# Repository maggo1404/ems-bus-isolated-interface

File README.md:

# Optocoupler Isolated EMS Bus Interface for ESP32 / Raspberry Pi

An open-source hardware interface designed to safely connect microcontrollers (like ESP32 or Raspberry Pi) to the **EMS (Energy Management System)** bus used by Bosch, Buderus, Junkers, IVT and Nefit heating systems.

## Key Features

* **Galvanic Isolation:** Full optical/digital isolation protecting your microcontroller and smart home infrastructure from high-voltage spikes or ground loops on the boiler side.
* **4-Pin Output Interface:** Simple connection via `GND`, `Rx`, `Tx`, and `3.3V`.
* **High Compatibility:** Designed to be fully compatible with popular open-source firmware [EMS-ESP32](https://github.com/emsesp/EMS-ESP32).
* **Compact DIY Design:** Two-layer PCB created in Autodesk Eagle, optimized for easy manual soldering or cheap fabrication (JLCPCB, PCBWay).

---

## Technical Specifications

* **Input:** 2-wire EMS Bus (Non-polarized)
* **Output:** 3.3V Logic Levels (`Rx` from EMS to MCU, `Tx` from MCU to EMS)
* **Power Supply:** 
  * EMS Side: Powered directly from the EMS bus line.
  * MCU Side: Powered from the connected microcontroller via the `3.3V` pin (requires approx. 10 mA).
* **Isolation Voltage:** Min 3 kV (achieved via optocouplers 6N137 and 6N136).

---

## Repository Structure

* `/hardware` - Original Autodesk Eagle design files (`.sch`, `.brd` and `.lbr`).
* `/gerber` - Production-ready Gerber and Drill files (Excellon) for easy PCB manufacturing.
* `/bom` - Bill of Materials with component specifications.
* `/assets` - Images and pdf files.

---

## Schematic & PCB Preview
You can notice the strict galvanic isolation of both parts. They are bridged only by optocouplers.

---

## How to Order and Build

1. **Manufacture the PCB:** Download the ZIP file from the `/gerber` folder and upload it to any PCB manufacturer (e.g., JLCPCB, PCBWay, OSH Park). Choose a standard 1.6mm thickness, 2-layer option.
2. **Buy Components:** Refer to the [BOM.csv](./bom/BOM.csv) or [BOM.pdf](./bom/BOM.pdf) file for the exact part list. 
3. **Assembly:** Solder the components starting from the lowest profile parts (resistors, diodes) to the highest (connectors, optocouplers).

---

## Connection Diagram

### EMS Bus Side
Connect the 2-wire terminal to your boiler's EMS service jack or thermostat line.

### Microcontroller Side (e.g., ESP32 running EMS-ESP)

| Interface Pin | ESP32 Pin | Description |
| --- | --- | --- |
| **GND** | GND | Ground reference (isolated side) |
| **Rx** | GPIO 5 (Rx) | Connect to ESP32 Rx pin |
| **Tx** | GPIO 17 (Tx) | Connect to ESP32 Tx pin |
| **3.3V** | 3.3V | Power input for the isolated side |

---

## Software Integration

This hardware is verified to work with:
* **EMS-ESP32 Firmware:** Set the board profile to *Custom* and configure your chosen Rx/Tx pins in the web interface.

---

## Notes on some components

**C12 - 2200µF/25V**  
Originally I wanted to use a capacitor with a capacity of 1000µF. During testing, everything seemed to be fine. However, for dimensional reasons, I also tried a capacitor with a capacity of 470µF, because it fit into the intended box even in the normal position ("vertical"). However, in practice it turned out that with this capacitor the communication error rate increased sharply. Of course, this was not desirable, so I used a larger capacitor (with sufficient margin).

**OC1 and OC2 - 6N137 and 6N136**  
For the Rx direction (EMS -> ESP32), I chose an optocoupler of the 6N137SM-ISO type. It is fast enough and guarantees problem-free communication. In the opposite direction, the cheaper 6N136S-TA1-L is more than enough. Both optocouplers are in an SMD8 package with gull-wing pins.

**R2, R3 and R4 - 68Ω**  
The resistors are in a R2010 type case, so they should last with a large margin. Regular resistors in a R0805 case would be overloaded if used in this way and the connection would not be reliable in the long term.

**U1 - LM393**  
I used the LMV393IDR type.
It is fast enough, suitable for 5V power supply, has low consumption and has open collector outputs.

**U2 - JW5017S**  
You can also use the (perhaps more affordable) RY8310.

---

## Assembled board
Finally, you can see some photos of the fully assembled PCB including the installation in the box and the connection to the ESP32-S3 development kit. I have also added one screenshot showing the statistics of Data Traffic after about 90 hours of operation.

---

## License & Disclaimer

This project is licensed under the Creative Commons Attribution-NonCommercial-ShareAlike 4.0 International License (CC BY-NC-SA 4.0). 

* **Non-Commercial:** The hardware design files were created using the free/personal-use tier of Autodesk Eagle and are strictly intended for non-commercial, educational, and DIY purposes.
* **ShareAlike:** If you remix, transform, or build upon the material, you must distribute your contributions under the same license.

**Disclaimer:** Working with heating appliances carries inherent risks. Improper connection can damage your boiler's mainboard. Use this hardware at your own risk. The author is not responsible for any damage caused by using this design.

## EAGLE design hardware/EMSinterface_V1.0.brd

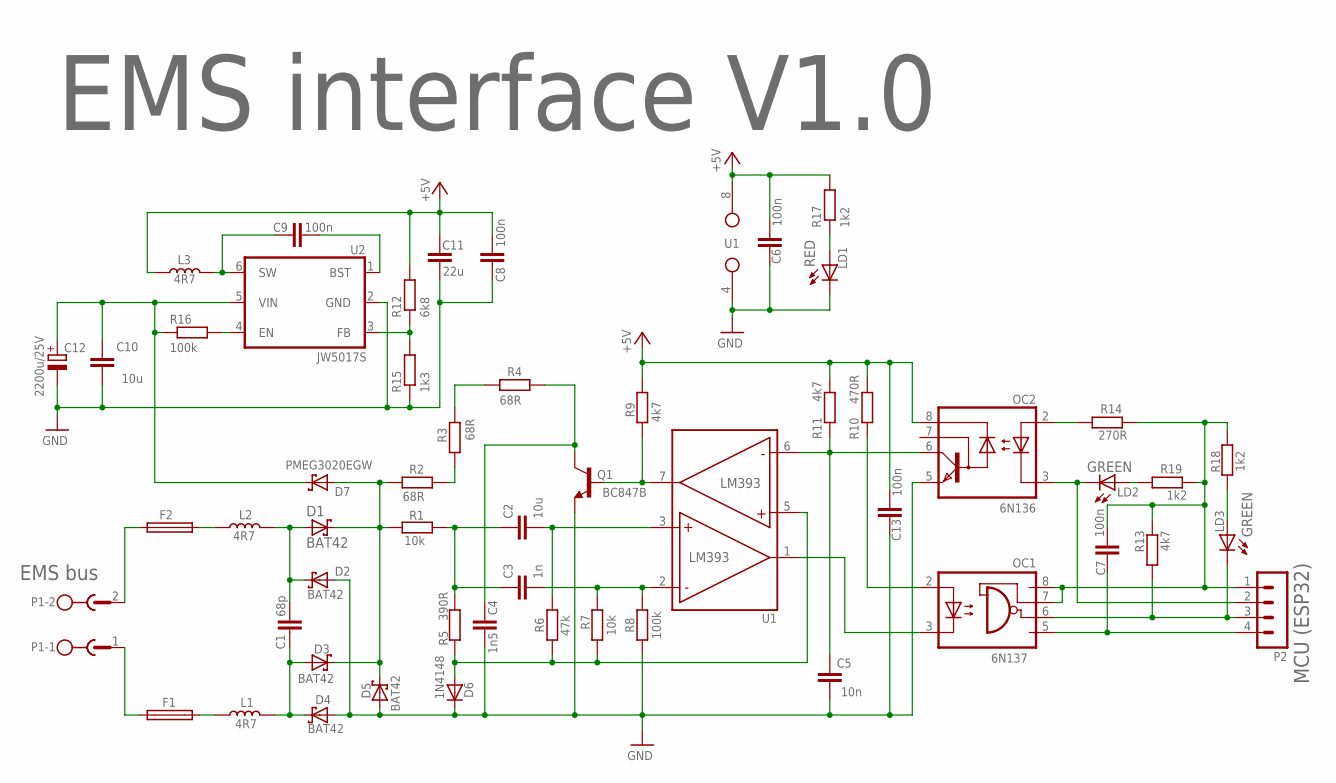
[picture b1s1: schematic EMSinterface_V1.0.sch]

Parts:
C1: 68p; C0805K
C2, C10: 10u; C0805K
C3: 1n; C0805K
C4: 1n5; C0805K
C5: 10n; C0805K
C6, C7, C8, C9, C13: 100n; C0805K
C11: 22u; C1206
C12: 2200u/25V; E5-10,5
D1, D2, D3, D4, D5: BAT42; SOD123
D6: 1N4148; SOD123
D7: PMEG3020EGW; SOD123
F1, F2: FUSE0805R0805; R0805
L1, L2: 4R7; L3225M
L3: 4R7; INDUCTOR_0520
LD1: RED; CHIP-LED0805
LD2, LD3: GREEN; CHIP-LED0805
OC1: 6N137; SO8-GW300
OC2: 6N136; SO8-GW300
P1: MSTBA2
P2: CON-LSTB_0408; CON-LSTB_04
Q1: BC847B; SOT23
R1, R7: 10k; R0805
R2, R3, R4: 68R; R2010
R5: 390R; R0805
R6: 47k; R0805
R8, R16: 100k; R0805
R9, R11, R13: 4k7; R0805
R10: 470R; R0805
R12: 6k8; R0805
R14: 270R; R0805
R15: 1k3; R0805
R17, R18, R19: 1k2; R0805
U1: LMV393IDR; LM393
U2: JW5017S; SOT23-6

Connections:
+5V: C6.2, C8.1, C11.1, C13.2, L3.1, OC2.8 (VCC), R9.2, R10.2, R11.2, R12.2, R17.2, U1.8 (VCC)
GND: C4.1, C5.1, C6.1, C8.2, C10.1, C11.2, C12.-, C13.1, D2.A, D4.A, D5.A, D6.C, LD1.C, OC2.5 (GND), Q1.2 (E), R8.1, R15.1, U1.4 (GND), U2.2 (GND)
MCUGND: C7.1, OC1.5 (GND), P2.4 (5)
MCURX: LD3.C, OC1.6 (VO), P2.3 (4), R13.1
MCUTX: LD2.C, OC2.3 (C), P2.2 (3)
MCUVCC: C7.2, OC1.7 (VE), OC1.8 (VCC), P2.1 (2), R13.2, R14.1, R18.2, R19.1
unnamed: F2.2, L2.1
unnamed: F1.2, L1.1
unnamed: C1.1, D1.A, D2.C, L2.2
unnamed: C1.2, D3.A, D4.C, L1.2
unnamed: F2.1, P1.2
unnamed: D1.C, D3.C, D5.C, D7.A, R1.1, R2.1
unnamed: D6.A, R5.1, R6.1, R7.1, U1.5 (IN+)
unnamed: C2.1, C3.1, R1.2, R5.2
unnamed: C2.2, R6.2, U1.3 (IN+)
unnamed: C3.2, R7.2, R8.2, U1.2 (IN-)
unnamed: R3.2, R4.1
unnamed: R2.2, R3.1
unnamed: C4.2, Q1.3 (C), R4.2
unnamed: Q1.1 (B), R9.1, U1.7 (OUT)
unnamed: C5.2, OC2.6 (VO), R11.1, U1.6 (IN-)
unnamed: OC1.2 (A), R10.1
unnamed: F1.1, P1.1
unnamed: OC1.3 (C), U1.1 (OUT)
unnamed: OC2.2 (A), R14.2
unnamed: LD2.A, R19.2
unnamed: R12.1, R15.2, U2.3 (FB)
unnamed: LD3.A, R18.1
unnamed: C9.1, U2.1 (BST)
unnamed: C9.2, L3.2, U2.6 (SW)
unnamed: LD1.A, R17.1
unnamed: R16.2, U2.4 (EN)
VIN: C10.2, C12.+, D7.C, R16.1, U2.5 (VIN)

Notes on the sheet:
EMS interface V1.0
EMS bus
MCU (ESP32)

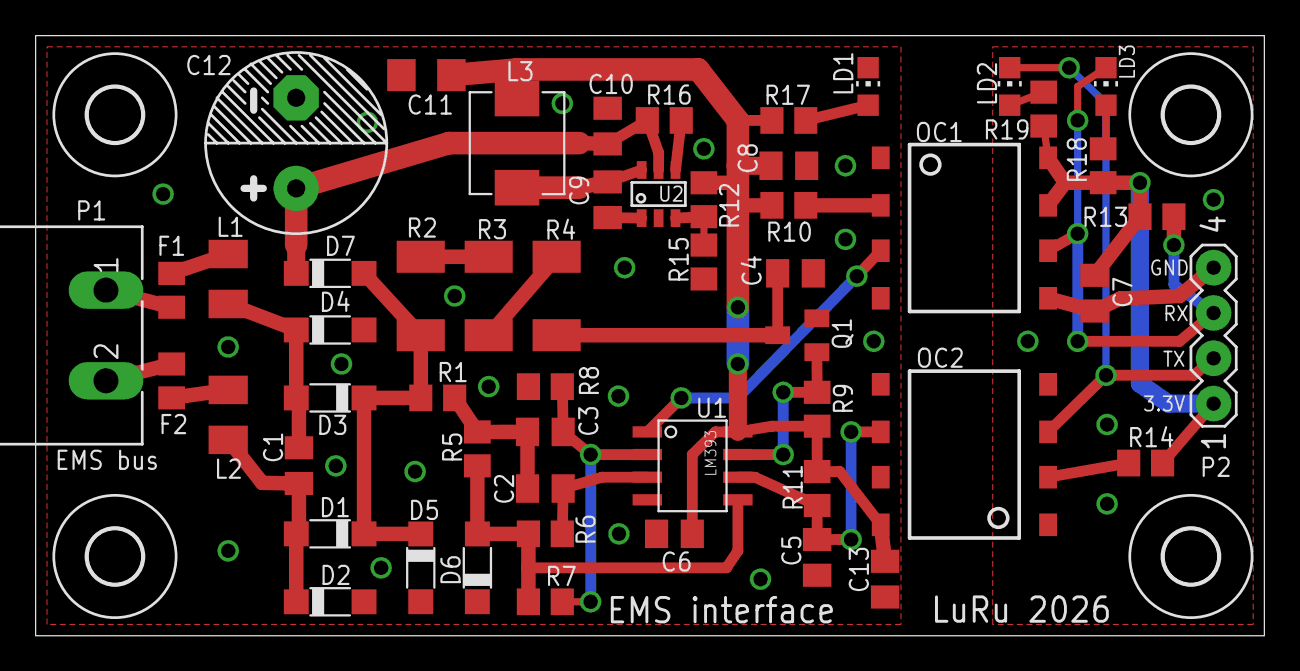
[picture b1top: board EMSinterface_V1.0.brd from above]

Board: 2 copper layers, 68.9 x 33.6 mm, 58 parts (0 on the bottom side), 33 nets.

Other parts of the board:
U$6, U$7, U$8, U$9: 3,0

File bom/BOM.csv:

"Qty";"Value";"Device";"Package";"Parts";"Description";"";
"1";"2200u/25V";"CPOL-EUE5-10.5";"E5-10,5";"C12";"POLARIZED CAPACITOR, European symbol";"";
"2";"100k";"R-EUR0805";"R0805";"R8, R16";"RESISTOR, European symbol";"";
"5";"100n";"C-EUC0805K";"C0805K";"C6, C7, C8, C9, C13";"CAPACITOR, European symbol";"";
"2";"10k";"R-EUR0805";"R0805";"R1, R7";"RESISTOR, European symbol";"";
"1";"10n";"C-EUC0805K";"C0805K";"C5";"CAPACITOR, European symbol";"";
"2";"10u";"C-EUC0805K";"C0805K";"C2, C10";"CAPACITOR, European symbol";"";
"1";"1N4148";"1N4148";"SOD123";"D6";"DIODE";"";
"3";"1k2";"R-EUR0805";"R0805";"R17, R18, R19";"RESISTOR, European symbol";"";
"1";"1k3";"R-EUR0805";"R0805";"R15";"RESISTOR, European symbol";"";
"1";"1n";"C-EUC0805K";"C0805K";"C3";"CAPACITOR, European symbol";"";
"1";"1n5";"C-EUC0805K";"C0805K";"C4";"CAPACITOR, European symbol";"";
"1";"22u";"C-EUC1206";"C1206";"C11";"CAPACITOR, European symbol";"";
"1";"270R";"R-EUR0805";"R0805";"R14";"RESISTOR, European symbol";"";
"1";"390R";"R-EUR0805";"R0805";"R5";"RESISTOR, European symbol";"";
"1";"470R";"R-EUR0805";"R0805";"R10";"RESISTOR, European symbol";"";
"1";"47k";"R-EUR0805";"R0805";"R6";"RESISTOR, European symbol";"";
"1";"4R7";"INDUCTOR";"INDUCTOR_0520";"L3";"";"";
"2";"4R7";"INDUCTORL3225M";"L3225M";"L1, L2";"";"";
"3";"4k7";"R-EUR0805";"R0805";"R9, R11, R13";"RESISTOR, European symbol";"";
"3";"68R";"R-EUR2010";"R2010";"R2, R3, R4";"RESISTOR, European symbol";"";
"1";"68p";"C-EUC0805K";"C0805K";"C1";"CAPACITOR, European symbol";"";
"1";"6N136";"6N136SSMD";"SO8-GW300";"OC2";"";"";
"1";"6N137";"6N137SSMD";"SO8-GW300";"OC1";"MOTOROLA OPTO COUPLER";"";
"1";"6k8";"R-EUR0805";"R0805";"R12";"RESISTOR, European symbol";"";
"5";"BAT42";"SCHOTTKYSOD123";"SOD123";"D1, D2, D3, D4, D5";"Schottky Power Rectifier";"";
"1";"BC847B";"BC847BBSMD";"SOT23";"Q1";"NPN Transistor";"";
"1";"CON-LSTB_0408";"CON-LSTB_0408";"CON-LSTB_04";"P2";"";"";
"2";"FUSE0805R0805";"FUSE0805R0805";"R0805";"F1, F2";"Fuse";"";
"2";"GREEN";"LED0805CHIP-LED0805";"CHIP-LED0805";"LD2, LD3";"LED";"";
"1";"JW5017S";"JW5017S";"SOT23-6";"U2";"";"";
"1";"LM393";"LM393";"LM393";"U1";"";"";
"1";"MSTBA2";"MSTBA2";"MSTBA2";"P1";"";"";
"1";"PMEG3020EGW";"SCHOTTKYSOD123";"SOD123";"D7";"Schottky Power Rectifier";"";
"1";"RED";"LED0805CHIP-LED0805";"CHIP-LED0805";"LD1";"LED";"";

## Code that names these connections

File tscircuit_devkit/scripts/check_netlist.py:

#!/usr/bin/env python3
"""Check the full V2.0 board (dist/index/circuit.json) against docs/netlist_v1.json and DESIGN_SPEC.

1. All 33 V1 nets (incl. P2 -> V3V3/MCU_TX/MCU_RX/GND): the 29 EMS-only nets must match pin-for-pin
   (JLC pad numbering, see PAD_SWAP); the 4 shared MCU nets (MCUGND, MCUVCC, MCURX, MCUTX) must contain all V1 pins
   (V2 adds ESP32/USB pins to them, they are listed as 'extra').
2. New MCU-side nets of the DevKitC variant (ESP_TX, P2_3V3, GPIO2 LED, DevKitC socket pins J1/J3): pins must be on one net,
   different nets must not be shorted, EMS and MCU nets must not be shorted.
Usage: python3 scripts/check_netlist.py [circuit.json] [docs/netlist_v1.json]
"""
import json, sys
sys.path.insert(0, __file__.rsplit("/", 1)[0])
from netlib import load, Conn

cjp = sys.argv[1] if len(sys.argv) > 1 else "dist/index/circuit.json"
refp = sys.argv[2] if len(sys.argv) > 2 else "docs/netlist_v1.json"
c = Conn(load(cjp))
ref = json.load(open(refp))
NAME = {"+5V": "V5_EMS", "GND": "GND_EMS", "VIN": "EMS_VIN", "MCUGND": "GND", "MCUVCC": "V3V3", "MCURX": "MCU_RX", "MCUTX": "MCU_TX"}
SHARED = {"MCUGND", "MCUVCC", "MCURX", "MCUTX"}
# JLC pad numbering: BAT42W (D1-D5) and green LEDs (LD2, LD3): pad1 = anode; D6, D7, LD1: pad1 = cathode
ANODE_FIRST = {"D1", "D2", "D3", "D4", "D5", "LD2", "LD3"}


def cvt(pin):
    r, pad = pin.split(".")
    if r.startswith("D") or r.startswith("LD"):
        pad = {"A": "1", "C": "2"}[pad] if r in ANODE_FIRST else {"C": "1", "A": "2"}[pad]
    elif r == "C12":
        pad = {"+": "1", "-": "2"}.get(pad, pad)
    else:
        pad = {"+": "1", "-": "2"}.get(pad, pad)
    return "%s.%s" % (r, pad)


pin2grp = {}
for g, d in c.groups.items():
    for p in d["pins"]:
        pin2grp[p] = g
ok = True
print("== V1 nets (%d) ==" % len(ref["nets"]))
for n in ref["nets"]:
    exp = {cvt(p) for p in n["pins"]}
    # V2: the single 2200uF C12 is replaced by C12 + C14 (2 x 1000uF SMD in parallel, same nets)
    exp |= {"C14." + p.split(".")[1] for p in exp if p.startswith("C12.")}
    # V2: C30 (100 nF) is added in parallel to the buck input capacitor C10 (same nets, R5 M2)
    exp |= {"C30." + p.split(".")[1] for p in exp if p.startswith("C10.")}
    name = NAME.get(n["name"], n["name"])
    if n["name"] == "MCUVCC":  # V2: P2 pin 1 hangs on net P2_3V3 behind the open solder jumper JP2
        exp.discard("P2.1")
    gs = {pin2grp.get(p) for p in exp}
    if len(gs) != 1 or None in gs:
        ok = False
        missing = sorted(p for p in exp if pin2grp.get(p) is None)
        print("FAIL %-8s (%s) pins not on one net; unconnected=%s groups=%d" % (n["name"], name, missing, len(gs)))
        continue
    g = gs.pop()
    got = c.groups[g]["pins"]
    extra = sorted(got - exp)
    names = sorted(c.groups[g]["names"])
    if n["name"] in SHARED:
        status = "OK  " if name in names else "FAIL"
        if status == "FAIL":
            ok = False
        print("%s %-8s -> %s  (+%d V2 pins: %s)" % (status, n["name"], names, len(extra), ",".join(extra[:40])))
    else:
        if extra:
            ok = False
            print("FAIL %-8s extra pins %s" % (n["name"], extra))
        else:
            print("OK   %-8s -> %s" % (n["name"], names))

# ---- new MCU nets (DESIGN_SPEC / src/mcu-side.tsx).  pins as Ref.pin number ----
# DevKitC variant: J1 / J3 = 1x22 sockets of the ESP32-S3-DevKitC-1 v1.1 (Espressif header table, docs/DEVKITC.md)
J1_OPEN_OK = {1: "3V3", 2: "3V3", 5: "GPIO5", 10: "GPIO17", 22: "GND"}   # J1 pins that carry a net
J3_OPEN_OK = {1: "GND", 5: "GPIO2", 21: "GND", 22: "GND"}                 # J3 pins that carry a net
NEW = {
    "V3V3": ["J1.1", "J1.2", "JP2.1", "R27.2"],
    "GND": ["J1.22", "J3.1", "J3.21", "J3.22", "LD4.2", "P2.4"],
    "MCU_RX": ["J1.5", "OC1.6", "P2.3"],
    "ESP_TX": ["J1.10", "JP1.1"],
    "MCU_TX": ["JP1.2", "R27.1", "OC2.3", "P2.2"],
    "P2_3V3": ["JP2.2", "P2.1"],
    "GPIO2_LED": ["J3.5", "R22.1"],
    "LED_R22": ["R22.2", "LD4.1"],
}
print("\n== new MCU nets ==")
roots = {}
for name, pins in NEW.items():
    pins = [p for p in pins if p != "GND_ANCHOR"]
    if not pins:  # SBU1/SBU2 (J2.4, J2.10) are intentionally unconnected
        continue
    gs = {pin2grp.get(p) for p in pins}
    if len(gs) != 1 or None in gs:
        ok = False
        print("FAIL %-10s not one net: unconnected=%s" % (name, [p for p in pins if pin2grp.get(p) is None]))
        continue
    g = gs.pop()
    if name in ("UART0_GND",):
        continue
    nm = sorted(c.groups[g]["names"])
    if name in ("V3V3", "GND", "MCU_RX", "ESP_TX", "MCU_TX", "P2_3V3") and name not in nm:
        ok = False
        print("FAIL %-10s net names %s" % (name, nm))
        continue
    if g in roots:
        ok = False
        print("FAIL %-10s shorted with %s" % (name, roots[g]))
        continue
    roots[g] = name
    print("OK   %-10s -> %s (%d pins in net)" % (name, nm, len(c.groups[g]["pins"])))
# parts: LCSC numbers / values of the changed parts, every pad of USB-C / EPAD / tactile / shell on the right net
src = {x["name"]: x for x in c.cj if x["type"] == "source_component"}
for ref, mpn, lcsc in [("Q1", "BC817-40", "C20069155")]:
    comp = src.get(ref)
    got_l = (comp or {}).get("supplier_part_numbers", {}).get("jlcpcb", [])
    if not comp or comp.get("manufacturer_part_number") != mpn or lcsc not in got_l:
        ok = False
        print("FAIL part %s expected %s %s got %s" % (ref, mpn, lcsc, comp and (comp.get("manufacturer_part_number"), got_l)))
    else:
        print("OK   part %s = %s %s" % (ref, mpn, lcsc))
# JP2: V3V3 <-> P2_3V3 only through the (open) jumper: pins must be on DIFFERENT nets
if pin2grp.get("JP2.1") == pin2grp.get("JP2.2") or pin2grp.get("JP1.1") == pin2grp.get("JP1.2"):
    ok = False
    print("FAIL JP1/JP2 pins on one net (jumper not open)")
# DevKitC sockets: every pin except the ones above must be open (5V, RST, GPIO0 ... are NOT connected; 5V must never touch V3V3)
for ref, okp, n in (("J1", J1_OPEN_OK, 22), ("J3", J3_OPEN_OK, 22)):
    for i in range(1, n + 1):
        g = pin2grp.get("%s.%d" % (ref, i))
        if (i in okp) != (g is not None):
            ok = False
            print("FAIL %s.%d should be %s" % (ref, i, okp.get(i, "open (NC)")))
print("OK   J1/J3: only pins %s / %s are connected, the other %d pins are open" % (sorted(J1_OPEN_OK), sorted(J3_OPEN_OK), 44 - len(J1_OPEN_OK) - len(J3_OPEN_OK)))
# EMS/MCU separation by net names
EMS = lambda n: n.startswith("EMS_") or n in ("GND_EMS", "V5_EMS")
print("\n== EMS/MCU separation ==")
for g, d in c.groups.items():
    nms = d["names"]
    if any(EMS(n) for n in nms) and any(not EMS(n) for n in nms):
        ok = False
        print("FAIL net group mixes EMS and MCU names:", nms)
    if len(nms) > 1:
        ok = False
        print("FAIL net group has several names (short):", nms)
print("ALL OK" if ok else "FAILED")
sys.exit(0 if ok else 1)

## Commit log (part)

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2026-06-25 first public version
